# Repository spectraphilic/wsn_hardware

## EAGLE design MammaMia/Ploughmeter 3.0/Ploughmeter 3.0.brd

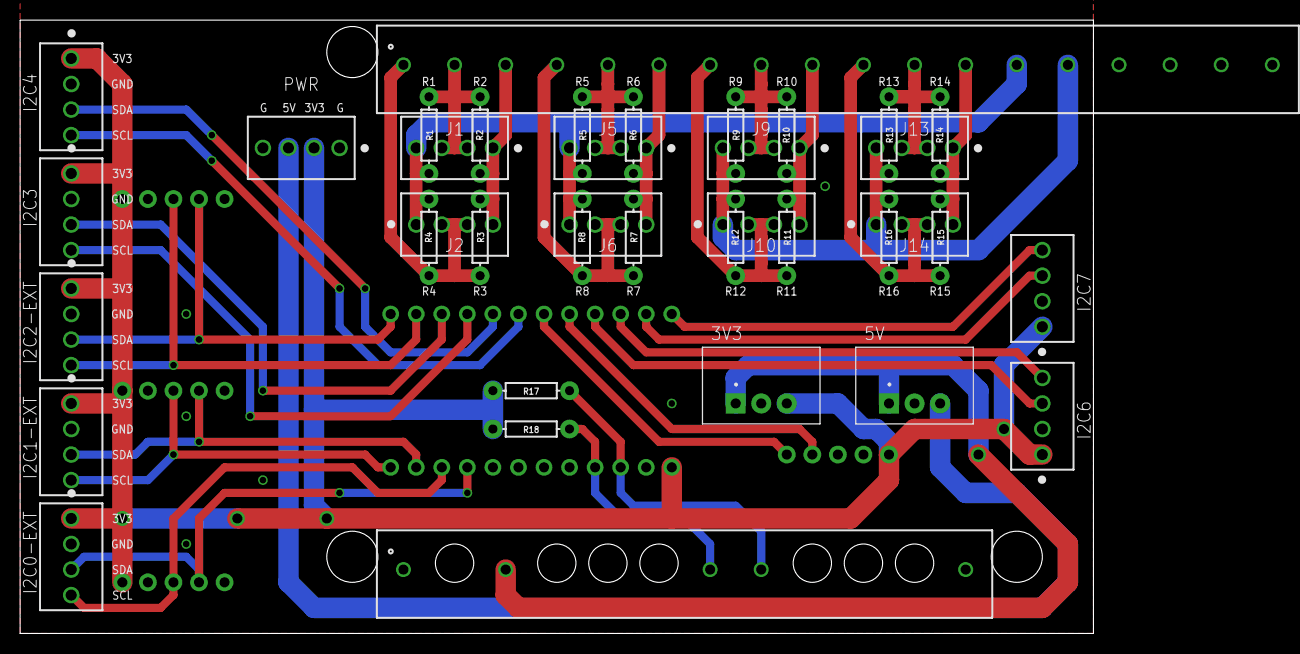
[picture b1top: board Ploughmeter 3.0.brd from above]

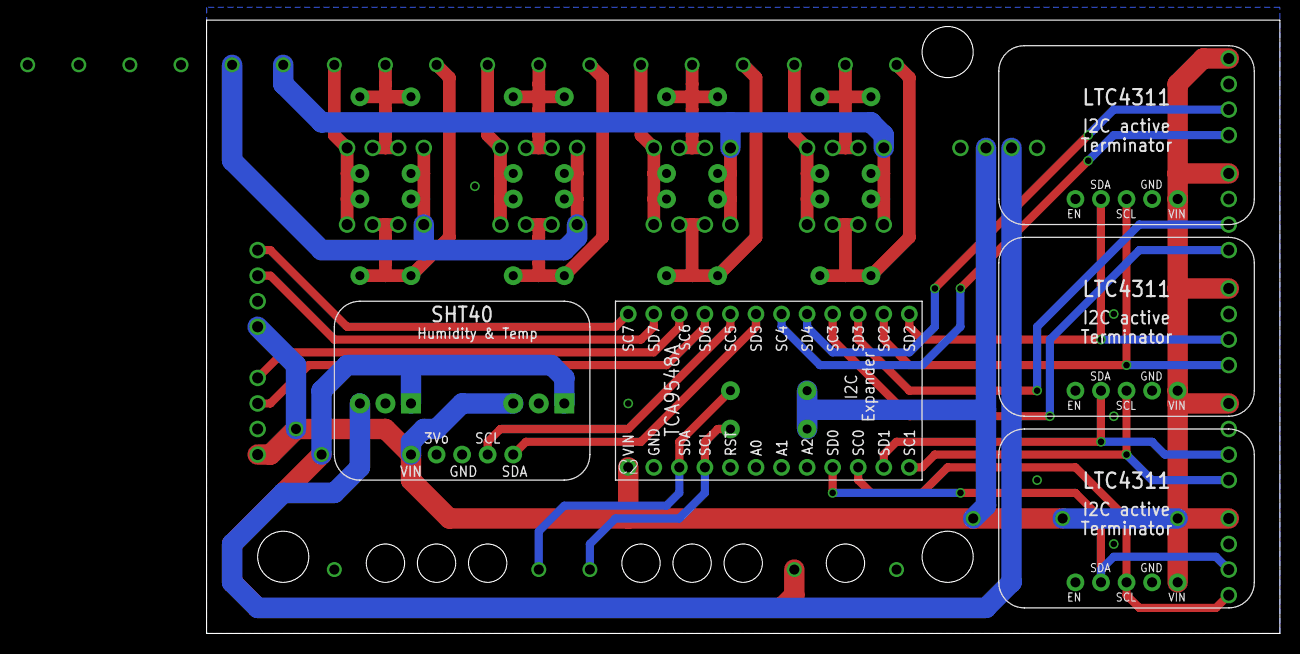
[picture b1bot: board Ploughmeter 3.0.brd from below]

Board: 2 copper layers, 106.7 x 61.0 mm, 44 parts (3 on the bottom side), 36 nets.

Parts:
3V3, 5V: 173010535
C1: WURTH_CONNECTORS_WR-TBL-PLUGGABLE-CONNECTOR_691311500018
C2: WURTH_CONNECTORS_WR-TBL-PLUGGABLE-CONNECTOR_691311500012
EX0, EX1, EX5: 1X05_ROUND_70
I2C0-EXT, I2C1-EXT, I2C2-EXT, I2C3, I2C4, I2C6, I2C7: 1725672; 1725672-4-2.54
J1, J2, J5, J6, J9, J10, J13, J14: 1725672; 1725672-4-2.54
JP2, JP4: 1X12_ROUND
JP5: 1X05_ROUND_70
PWR: 1725672; 1725672-4-2.54
R1, R2, R3, R4, R5, R6, R7, R8, R9, R10, R11, R12, R13, R14, R15, R16: 350; AXIAL-0.3
R17, R18: 10k; AXIAL-0.3

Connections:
0SCL: EX0.3, I2C0-EXT.4, JP2.10
0SDA: EX0.4, I2C0-EXT.3, JP2.9
1SCL: EX1.3, I2C1-EXT.4, JP2.12
1SDA: EX1.4, I2C1-EXT.3, JP2.11
2SCL: EX5.3, I2C2-EXT.4, JP4.2
2SDA: EX5.4, I2C2-EXT.3, JP4.1
3SCL: I2C3.4, JP4.4
3SDA: I2C3.3, JP4.3
3V3: 3V3.3, EX0.1, EX1.1, EX5.1, I2C0-EXT.1, I2C1-EXT.1, I2C2-EXT.1, I2C3.1, I2C4.1, I2C6.1, I2C7.1, JP2.1, JP5.1, PWR.2, R17.P$2, R18.P$2
4SCL: I2C4.4, JP4.6
4SDA: I2C4.3, JP4.5
5SCL: JP4.8, JP5.4
5SDA: JP4.7, JP5.5
5V: 5V.3, PWR.3
6SCL: I2C6.4, JP4.10
6SDA: I2C6.3, JP4.9
7SCL: I2C7.4, JP4.12
7SDA: I2C7.3, JP4.11
C1/SCL: C2.7, JP2.4, R18.P$1
C2/SDA: C2.8, JP2.3, R17.P$1
G1: 3V3.2, 5V.2, C2.1, C2.12, EX0.2, EX1.2, EX5.2, I2C0-EXT.2, I2C1-EXT.2, I2C2-EXT.2, I2C3.2, I2C4.2, I2C6.2, I2C7.2, JP2.2, JP5.3, PWR.1, PWR.4
SG1: C1.3, J1.1, J2.4, R2.P$1, R3.P$1
SG2: C1.6, J5.1, J6.4, R6.P$1, R7.P$1
SG3: C1.9, J9.1, J10.4, R10.P$1, R11.P$1
SG4: C1.12, J13.1, J14.4, R14.P$1, R15.P$1
SW12-2: 3V3.1, 5V.1, C2.3
U1: C1.1, J2.2, J2.3, R3.P$2, R4.P$1
U2: C1.2, J1.2, J1.3, R1.P$1, R2.P$2
U3: C1.4, J6.2, J6.3, R7.P$2, R8.P$1
U4: C1.5, J5.2, J5.3, R5.P$1, R6.P$2
U5: C1.7, J10.2, J10.3, R11.P$2, R12.P$1
U6: C1.8, J9.2, J9.3, R9.P$1, R10.P$2
U7: C1.10, J14.2, J14.3, R15.P$2, R16.P$1
U8: C1.11, J13.2, J13.3, R13.P$1, R14.P$2
U9: C1.13, J1.4, J2.1, J5.4, J6.1, R1.P$2, R4.P$2, R5.P$2, R8.P$2
U10: C1.14, J9.4, J10.1, J13.4, J14.1, R9.P$2, R12.P$2, R13.P$2, R16.P$2

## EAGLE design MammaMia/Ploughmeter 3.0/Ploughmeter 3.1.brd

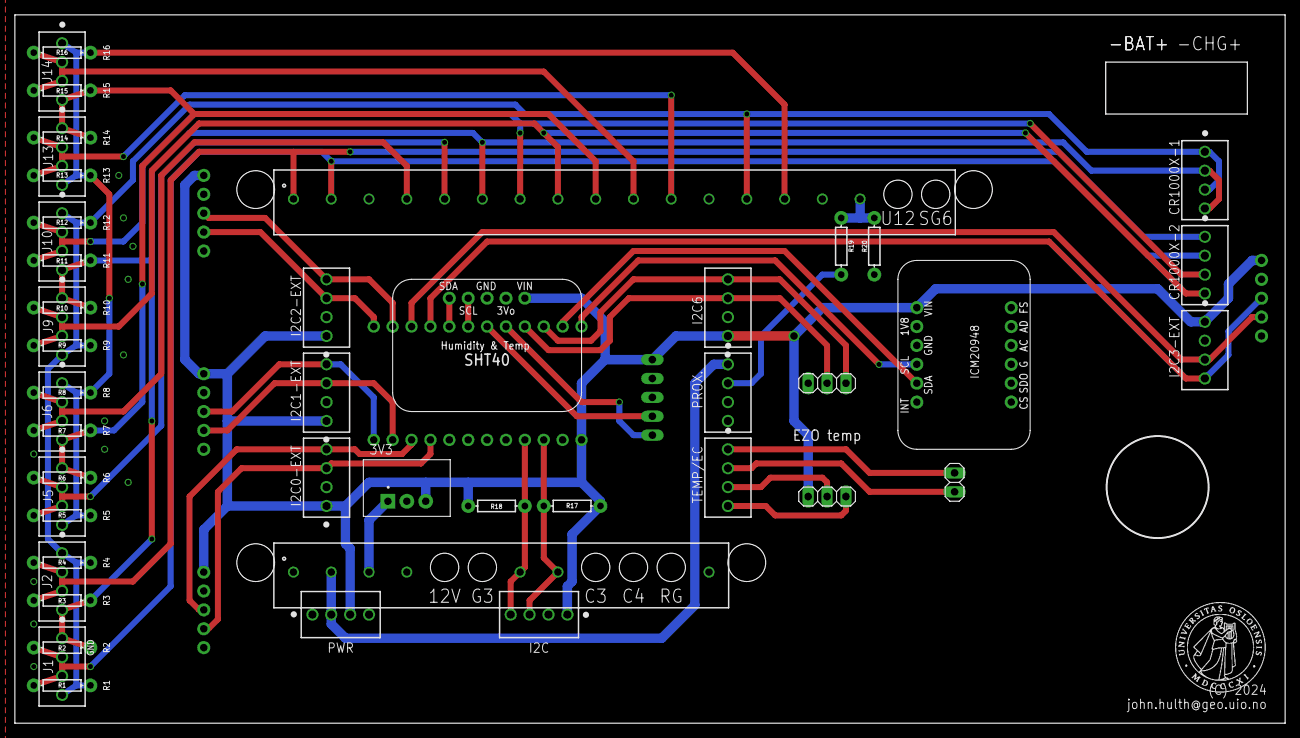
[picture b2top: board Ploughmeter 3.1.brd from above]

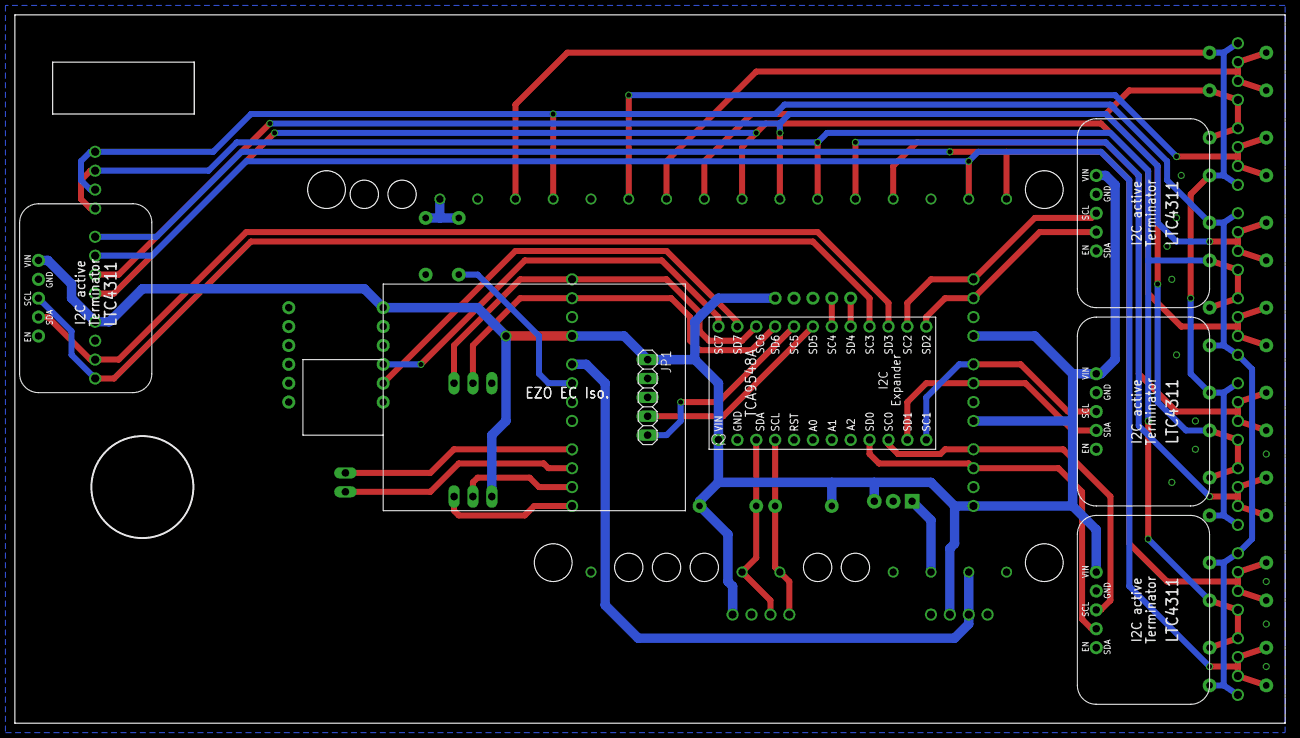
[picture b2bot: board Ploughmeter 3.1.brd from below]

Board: 2 copper layers, 170.8 x 95.2 mm, 56 parts (7 on the bottom side), 40 nets.

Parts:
3V3: 173010535
C1: WURTH_CONNECTORS_WR-TBL-PLUGGABLE-CONNECTOR_691311500018
C2: WURTH_CONNECTORS_WR-TBL-PLUGGABLE-CONNECTOR_691311500012
CR1000X-1, CR1000X-2: 1725672; 1725672-4-2.54
EX0, EX1: 1X05_ROUND_70
EX5: EX2; 1X05_ROUND_70
I2C, I2C0-EXT, I2C1-EXT, I2C2-EXT, I2C3-EXT, I2C6: 1725672; 1725672-4-2.54
J1, J2, J5, J6, J9, J10, J13, J14: 1725672; 1725672-4-2.54
JP1: 1X05
JP2, JP4: 1X12_ROUND
JP3: 1X02
JP5: 1X05_ROUND_70
JP6, JP7: 1X03
JP9: EX3; 1X05_ROUND_70
JP10, JP11: 1X06_ROUND_70
PROX.: 1725672; 1725672-4-2.54
PWR: 1725672; 1725672-4-2.54
R1, R2, R3, R4, R5, R6, R7, R8, R9, R10, R11, R12, R13, R14, R15, R16: 350; AXIAL-0.3
R17, R18: 10k; AXIAL-0.3
R19: 2k; AXIAL-0.3
R20: 1.3k; AXIAL-0.3
TEMP/EC: 1725672; 1725672-4-2.54
U$2: UIO-LOGO-BL

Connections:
0SCL: EX0.3, I2C0-EXT.4, JP2.10
0SDA: EX0.4, I2C0-EXT.3, JP2.9
1SCL: EX1.3, I2C1-EXT.4, JP2.12
1SDA: EX1.4, I2C1-EXT.3, JP2.11
2SCL: EX5.3, I2C2-EXT.4, JP4.2
2SDA: EX5.4, I2C2-EXT.3, JP4.1
3SCL: I2C3-EXT.4, JP4.4, JP9.3
3SDA: I2C3-EXT.3, JP4.3, JP9.4
3V3: 3V3.3, EX0.1, EX1.1, EX5.1, I2C.1, I2C0-EXT.1, I2C1-EXT.1, I2C2-EXT.1, I2C3-EXT.1, I2C6.1, JP1.1, JP2.1, JP5.1, JP7.1, JP9.1, JP10.1, PWR.3, R17.P$2, R18.P$2
4SCL: JP4.6, JP5.4
4SDA: JP4.5, JP5.5
5SCL: JP1.5, JP4.8
5SDA: JP1.4, JP4.7
6SCL: I2C6.4, JP4.10, JP6.1
6SDA: I2C6.3, JP4.9, JP6.2
7SCL: JP4.12, JP10.4
7SDA: JP4.11, JP10.5
C1/SCL: C2.7, I2C.4, JP2.4, R18.P$1
C2/SDA: C2.8, I2C.3, JP2.3, R17.P$1
EC+: JP3.1, TEMP/EC.1
EC-: JP3.2, TEMP/EC.2
G1: 3V3.2, C1.15, C2.1, C2.4, C2.12, EX0.2, EX1.2, EX5.2, I2C.2, I2C0-EXT.2, I2C1-EXT.2, I2C2-EXT.2, I2C3-EXT.2, I2C6.2, JP1.3, JP2.2, JP5.3, JP6.3, JP9.2, JP10.3, PROX..3, PWR.1, PWR.4, R20.P$1
PROX+: PROX..2, R19.P$2
SG2: C1.6, CR1000X-1.2, CR1000X-1.4, J1.1, J2.4, J9.1, J10.4, R2.P$1, R3.P$1, R10.P$1, R11.P$1
SG3: C1.9, J5.1, J6.4, J13.1, J14.4, R6.P$1, R7.P$1, R14.P$1, R15.P$1
SW12-1: C2.2, PROX..1, PWR.2
SW12-2: 3V3.1, C2.3
T+: JP7.2, TEMP/EC.3
T-: JP7.3, TEMP/EC.4
U1: C1.1, CR1000X-2.1, J2.2, J2.3, R3.P$2, R4.P$1
U2: C1.2, CR1000X-2.2, J1.2, J1.3, R1.P$1, R2.P$2
U3: C1.4, J6.2, J6.3, R7.P$2, R8.P$1
U4: C1.5, J5.2, J5.3, R5.P$1, R6.P$2
U5: C1.7, CR1000X-2.3, J10.2, J10.3, R11.P$2, R12.P$1
U6: C1.8, CR1000X-2.4, J9.2, J9.3, R9.P$1, R10.P$2
U7: C1.10, J14.2, J14.3, R15.P$2, R16.P$1
U8: C1.11, J13.2, J13.3, R13.P$1, R14.P$2
U9: C1.13, CR1000X-1.1, CR1000X-1.3, J1.4, J2.1, J9.4, J10.1, R1.P$2, R4.P$2, R9.P$2, R12.P$2
U10: C1.14, J5.4, J6.1, J13.4, J14.1, R5.P$2, R8.P$2, R13.P$2, R16.P$2
U11: C1.16, R19.P$1, R20.P$2

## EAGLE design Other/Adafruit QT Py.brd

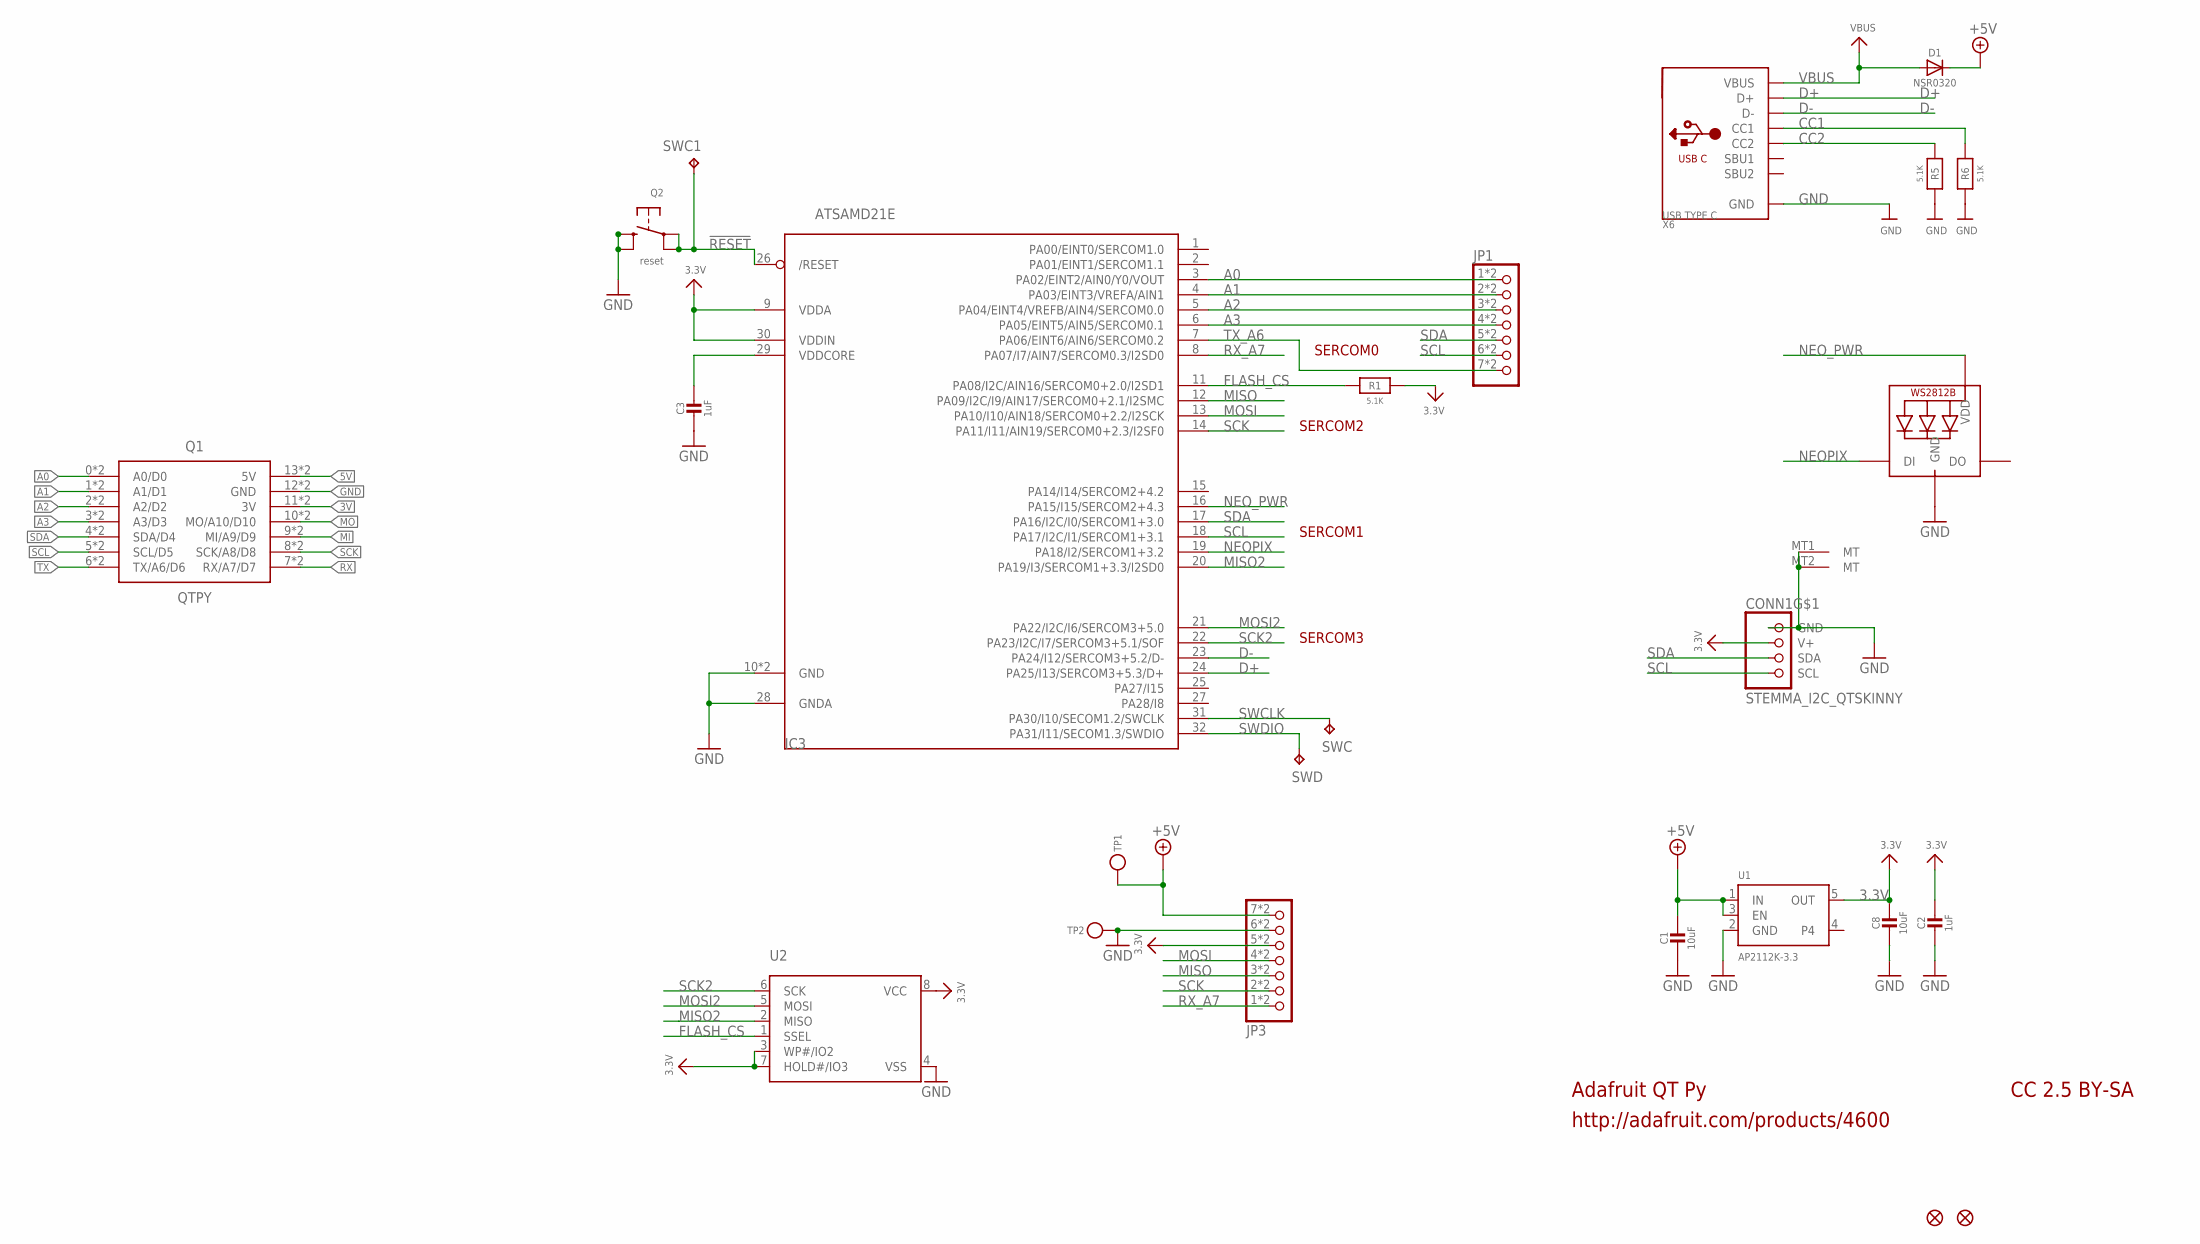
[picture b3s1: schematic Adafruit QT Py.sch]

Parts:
C1, C8: 10uF; _0805MP
C2, C3: 1uF; _0402NO
CONN1: STEMMA_I2C_QTSKINNY; JST_SH4_SKINNY
D1: NSR0320; SOD-323_MINI
IC3: ATSAMD21E; QFN32_5MM
JP1, JP3: HEADER-1X7_CASTEL; 1X07_CASTEL
LED1: WS2812B_SK6805_1515; SK6805_1515
Q1: QTPY
Q2: reset; BTN_KMR2_4.6X2.8
R1, R5, R6: 5.1K; _0402NO
SWC, SWC1: TPB1,27; B1,27
SWD: TPB1,27; B1,27
TP1, TP2: TESTPOINT_1X3; TESTPOINT_RECT_1X3MM
U1: AP2112K-3.3; SOT23-5
U2: SPIFLASH_8PIN; SOIC8_150MIL
U$6, U$8: FIDUCIAL_1MM
X6: USB TYPE C; USB_C_CUSB31-CFM2AX-01-X

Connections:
3.3V: C2.1, C8.1, CONN1.2 (V+), IC3.9 (VDDA), IC3.30 (VDDIN), JP3.5, JP3.5C (5), R1.1, U1.5 (OUT), U2.3 (WP#/IO2), U2.7 (HOLD#/IO3), U2.8 (VCC)
3V: Q1.11 (3V), Q1.11C (3V)
5V: Q1.13 (5V), Q1.13C (5V)
!RESET: IC3.26 (/RESET), Q2.A, Q2.A' (P1), SWC1.TP
+5V: C1.1, D1.C, JP3.7, JP3.7C (7), TP1.P$1, U1.1 (IN), U1.3 (EN)
A0: IC3.3 (PA02/EINT2/AIN0/Y0/VOUT), JP1.1, JP1.1C (1), Q1.0 (A0/D0), Q1.0C (A0/D0)
A1: IC3.4 (PA03/EINT3/VREFA/AIN1), JP1.2, JP1.2C (2), Q1.1 (A1/D1), Q1.1C (A1/D1)
A2: IC3.5 (PA04/EINT4/VREFB/AIN4/SERCOM0.0), JP1.3, JP1.3C (3), Q1.2 (A2/D2), Q1.2C (A2/D2)
A3: IC3.6 (PA05/EINT5/AIN5/SERCOM0.1), JP1.4, JP1.4C (4), Q1.3 (A3/D3), Q1.3C (A3/D3)
CC1: R6.2, X6.A5 (CC1)
CC2: R5.2, X6.B5 (CC2)
D+: IC3.24 (PA25/I13/SERCOM3+5.3/D+), X6.A6 (D+), X6.B6 (D+)
D-: IC3.23 (PA24/I12/SERCOM3+5.2/D-), X6.A7 (D-), X6.B7 (D-)
FLASH_CS: IC3.11 (PA08/I2C/AIN16/SERCOM0+2.0/I2SD1), R1.2, U2.1 (SSEL)
GND: C1.2, C2.2, C3.2, C8.2, CONN1.1 (GND), CONN1.MT1 (MT), CONN1.MT2 (MT), IC3.10 (GND), IC3.28 (GNDA), IC3.33 (GND), JP3.6, JP3.6C (6), LED1.4 (GND), Q1.12 (GND), Q1.12C (GND), Q2.B (S), Q2.B' (S1), R5.1, R6.1, TP2.P$1, U1.2 (GND), U2.4 (VSS), X6.A1B12 (GND), X6.B1A12 (GND)
MI: Q1.9 (MI/A9/D9), Q1.9C (MI/A9/D9)
MISO: IC3.12 (PA09/I2C/I9/AIN17/SERCOM0+2.1/I2SMC), JP3.3, JP3.3C (3)
MISO2: IC3.20 (PA19/I3/SERCOM1+3.3/I2SD0), U2.2 (MISO)
MO: Q1.10 (MO/A10/D10), Q1.10C (MO/A10/D10)
MOSI: IC3.13 (PA10/I10/AIN18/SERCOM0+2.2/I2SCK), JP3.4, JP3.4C (4)
MOSI2: IC3.21 (PA22/I2C/I6/SERCOM3+5.0), U2.5 (MOSI)
NEOPIX: IC3.19 (PA18/I2/SERCOM1+3.2), LED1.1 (DI)
NEO_PWR: IC3.16 (PA15/I15/SERCOM2+4.3), LED1.2 (VDD)
RX: Q1.7 (RX/A7/D7), Q1.7C (RX/A7/D7)
RX_A7: IC3.8 (PA07/I7/AIN7/SERCOM0.3/I2SD0), JP3.1, JP3.1C (1)
SCK: IC3.14 (PA11/I11/AIN19/SERCOM0+2.3/I2SF0), JP3.2, JP3.2C (2), Q1.8 (SCK/A8/D8), Q1.8C (SCK/A8/D8)
SCK2: IC3.22 (PA23/I2C/I7/SERCOM3+5.1/SOF), U2.6 (SCK)
SCL: CONN1.4 (SCL), IC3.18 (PA17/I2C/I1/SERCOM1+3.1), JP1.6, JP1.6C (6), Q1.5 (SCL/D5), Q1.5C (SCL/D5)
SDA: CONN1.3 (SDA), IC3.17 (PA16/I2C/I0/SERCOM1+3.0), JP1.5, JP1.5C (5), Q1.4 (SDA/D4), Q1.4C (SDA/D4)
SWCLK: IC3.31 (PA30/I10/SECOM1.2/SWCLK), SWC.TP
SWDIO: IC3.32 (PA31/I11/SECOM1.3/SWDIO), SWD.TP
TX: Q1.6 (TX/A6/D6), Q1.6C (TX/A6/D6)
TX_A6: IC3.7 (PA06/EINT6/AIN6/SERCOM0.2), JP1.7, JP1.7C (7)
VBUS: D1.A, X6.A4B9 (VBUS), X6.B4A9 (VBUS)
VDDCORE: C3.1, IC3.29 (VDDCORE)

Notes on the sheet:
Adafruit QT Py
http://adafruit.com/products/4600
CC 2.5 BY-SA
SERCOM0
SERCOM1
SERCOM2
SERCOM3

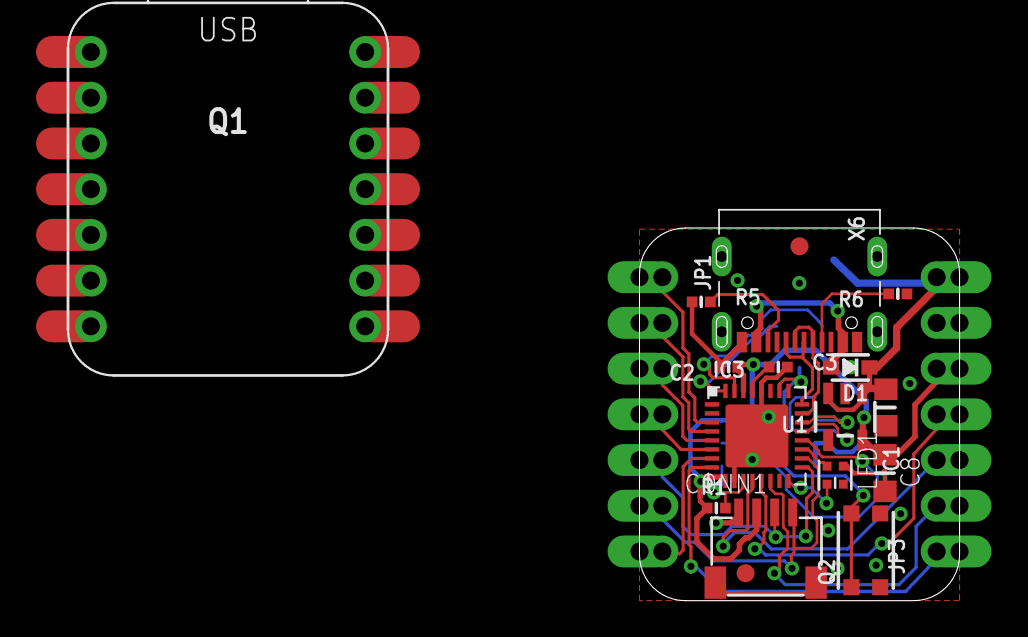
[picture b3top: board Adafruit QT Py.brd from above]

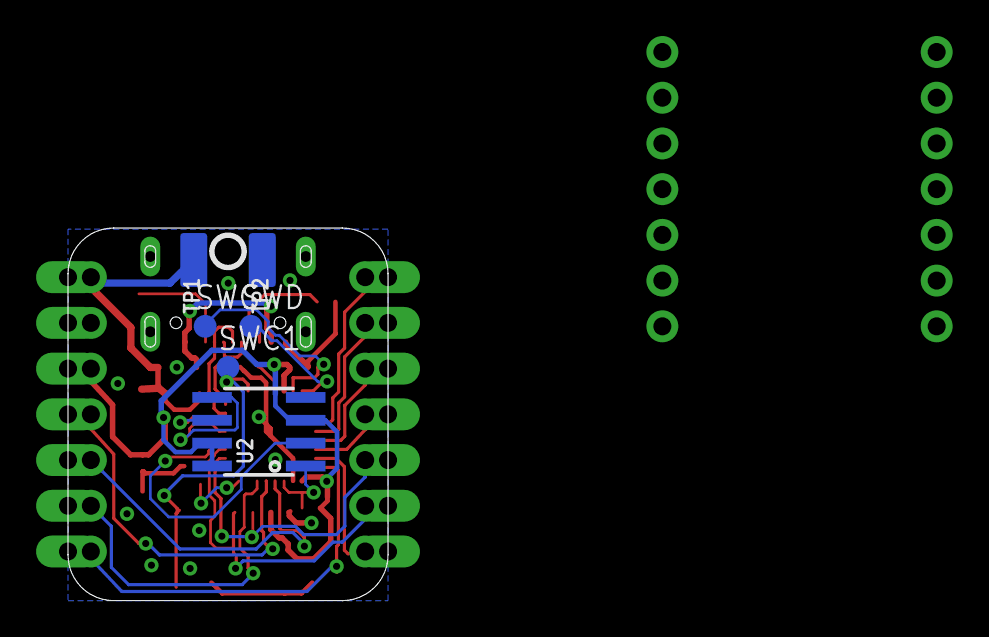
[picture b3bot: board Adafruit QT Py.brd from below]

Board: 2 copper layers, 17.8 x 20.7 mm, 28 parts (8 on the bottom side), 35 nets.

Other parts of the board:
U$11: QTPY_BOT
U$12: PCBFEAT-REV-040
U$13: QTPY_TOP

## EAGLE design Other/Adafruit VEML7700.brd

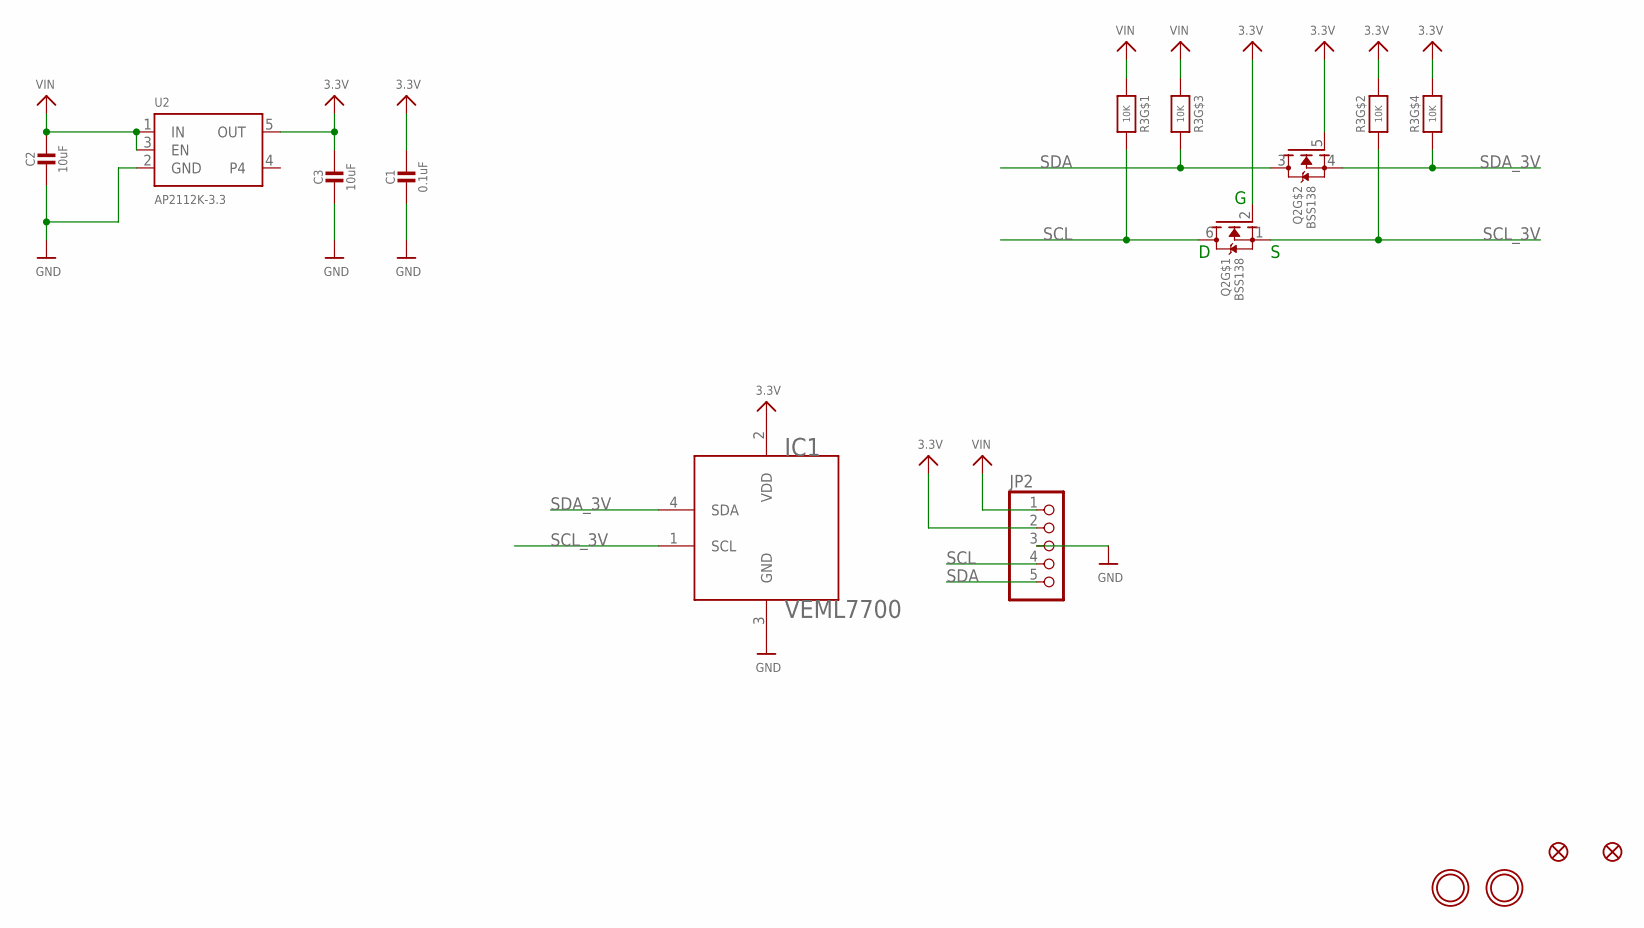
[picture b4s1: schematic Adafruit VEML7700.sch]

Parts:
C1: 0.1uF; 0603-NO
C2, C3: 10uF; 0805-NO
FID1, FID2: FIDUCIAL_1MM
IC1: VEML7700
JP2: HEADER-1X5ROUND; 1X05_ROUND
Q2: BSS138; SOT363
R3: 10K; RESPACK_4X0603
U2: AP2112K-3.3; SOT23-5
U$3, U$4: MOUNTINGHOLE2.5; MOUNTINGHOLE_2.5_PLATED

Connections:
3.3V: C1.1, C3.1, IC1.2 (VDD), JP2.2, Q2.2 (G), Q2.5 (G), R3.2 (1), R3.4 (1), U2.5 (OUT)
GND: C1.2, C2.2, C3.2, IC1.3 (GND), JP2.3, U2.2 (GND)
SCL: JP2.4, Q2.6 (D), R3.8 (2)
SCL_3V: IC1.1 (SCL), Q2.1 (S), R3.7 (2)
SDA: JP2.5, Q2.3 (D), R3.6 (2)
SDA_3V: IC1.4 (SDA), Q2.4 (S), R3.5 (2)
VIN: C2.1, JP2.1, R3.1, R3.3 (1), U2.1 (IN), U2.3 (EN)

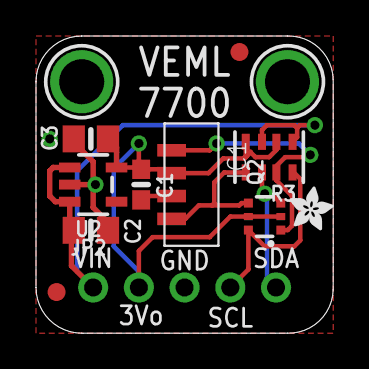
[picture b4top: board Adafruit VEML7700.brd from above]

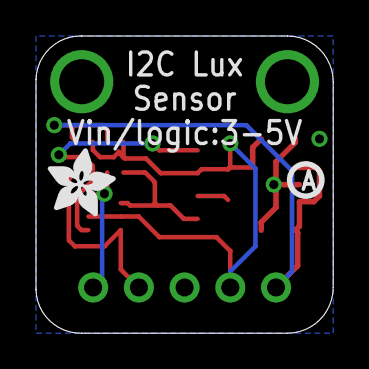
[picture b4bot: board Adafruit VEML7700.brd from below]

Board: 2 copper layers, 16.5 x 16.5 mm, 16 parts (3 on the bottom side), 7 nets.

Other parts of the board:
U$1: ADAFRUIT_3.5MM
U$8: ADAFRUIT_2.5MM
U$12: KATTNI_STOP
U$27: PCBFEAT-REV-040

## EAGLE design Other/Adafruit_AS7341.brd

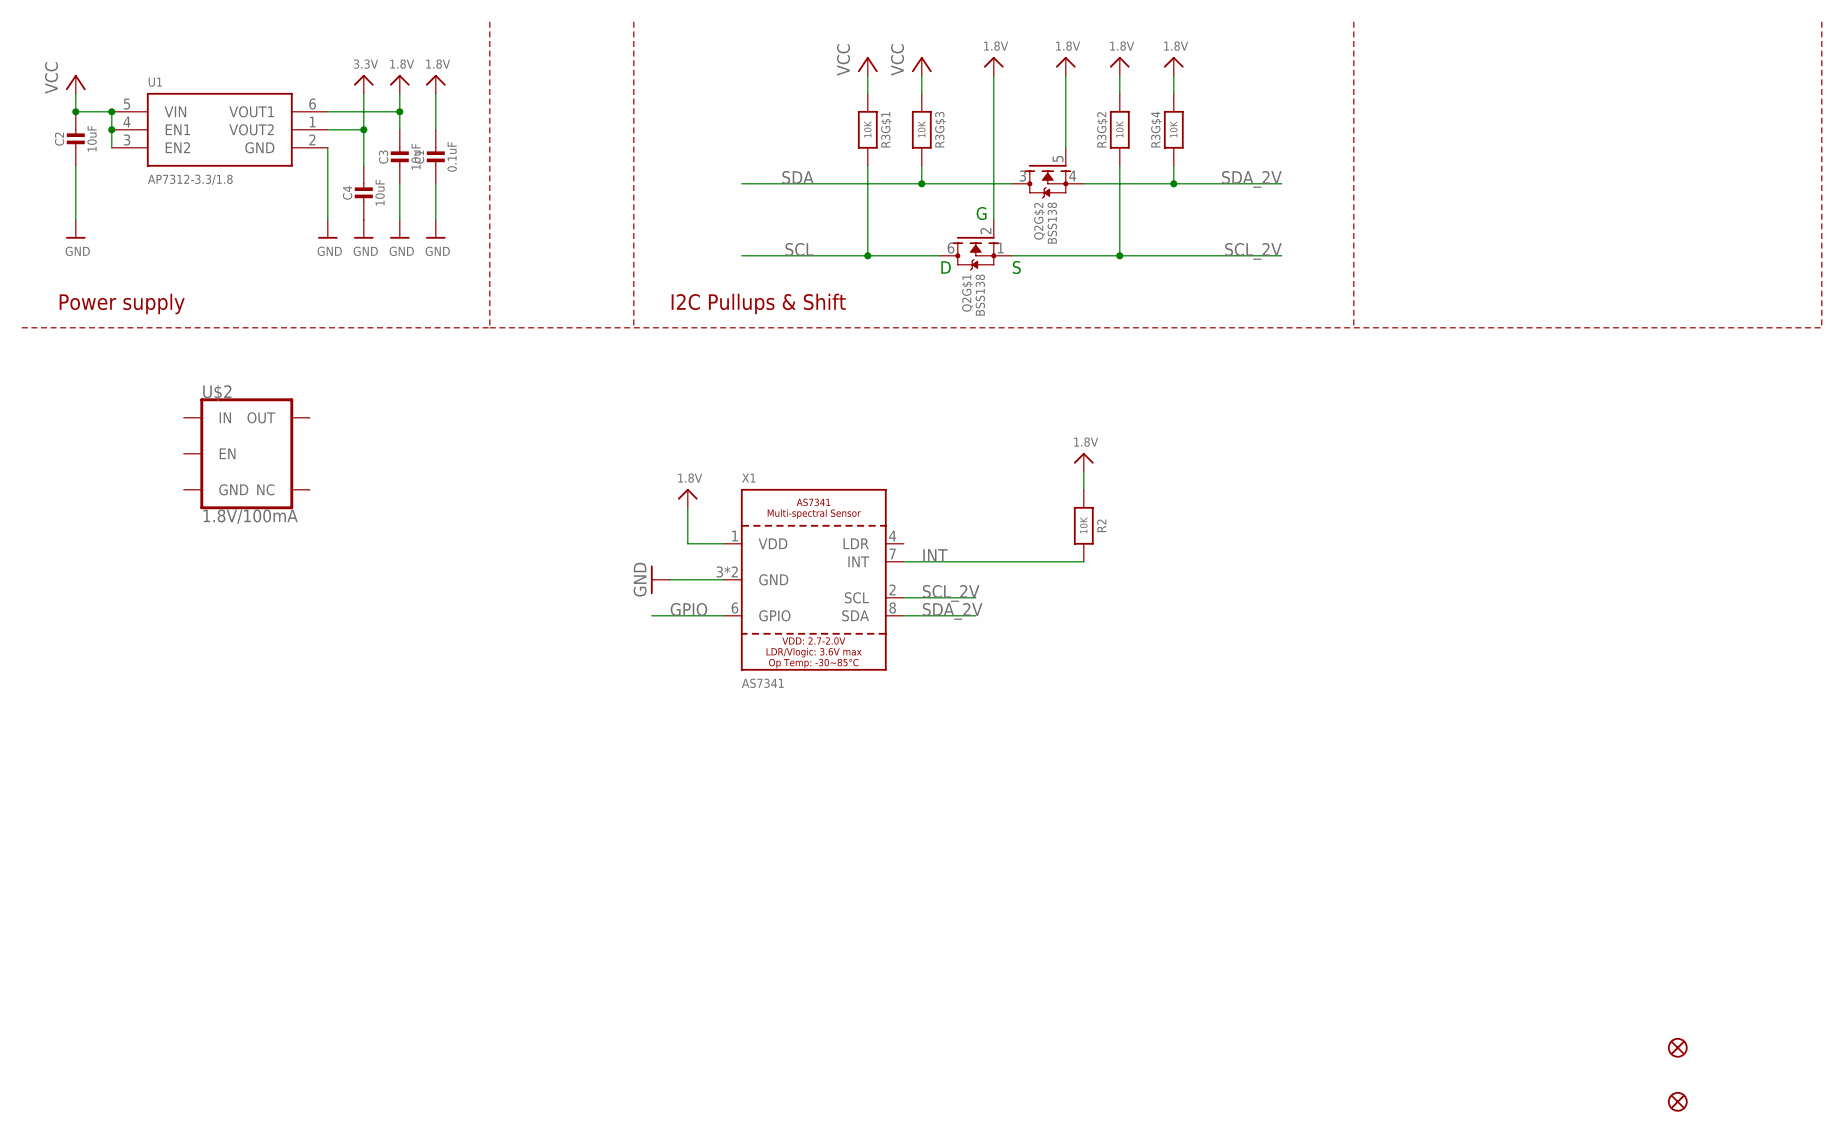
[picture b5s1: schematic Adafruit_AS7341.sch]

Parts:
C1: 0.1uF; 0603-NO
C2, C3, C4: 10uF; 0805-NO
FID3, FID4: FIDUCIAL_1MM
Q2: BSS138; SOT363
R2: 10K; 0603-NO
R3: 10K; RESPACK_4X0603
U1: AP7312-3.3/1.8; SOT23-6
U$2: 1.8V/100mA; SC70
X1: AS7341

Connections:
1.8V: C1.1, C3.1, Q2.2 (G), Q2.5 (G), R2.1, R3.2 (1), R3.4 (1), U1.6 (VOUT1), X1.1 (VDD)
3.3V: C4.1, U1.1 (VOUT2)
GND: C1.2, C2.2, C3.2, C4.2, U1.2 (GND), X1.3 (GND), X1.5 (GND)
GPIO: X1.6 (GPIO)
INT: R2.2, X1.7 (INT)
SCL: Q2.6 (D), R3.8 (2)
SCL_2V: Q2.1 (S), R3.7 (2), X1.2 (SCL)
SDA: Q2.3 (D), R3.6 (2)
SDA_2V: Q2.4 (S), R3.5 (2), X1.8 (SDA)
VCC: C2.1, R3.1, R3.3 (1), U1.3 (EN2), U1.4 (EN1), U1.5 (VIN)

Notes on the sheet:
I2C Pullups & Shift
Power supply

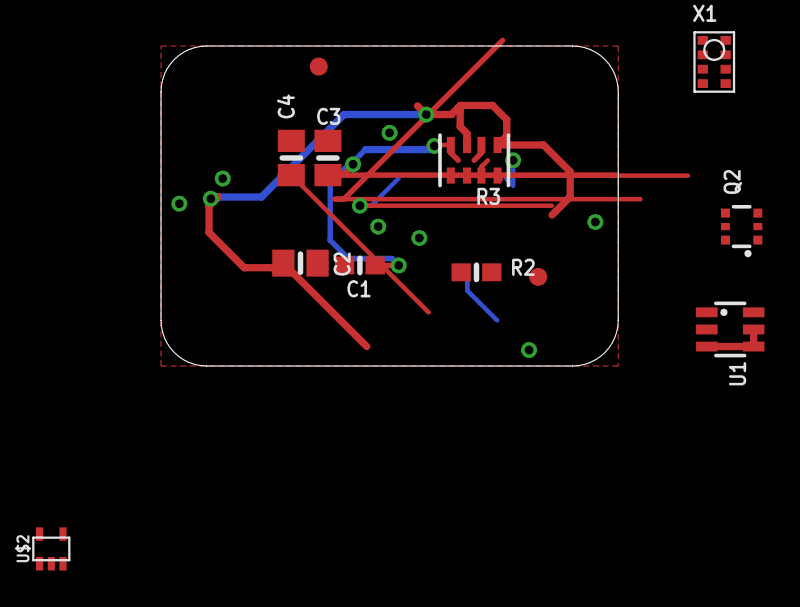
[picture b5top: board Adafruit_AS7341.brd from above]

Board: 2 copper layers, 25.4 x 17.8 mm, 12 parts (0 on the bottom side), 9 nets.

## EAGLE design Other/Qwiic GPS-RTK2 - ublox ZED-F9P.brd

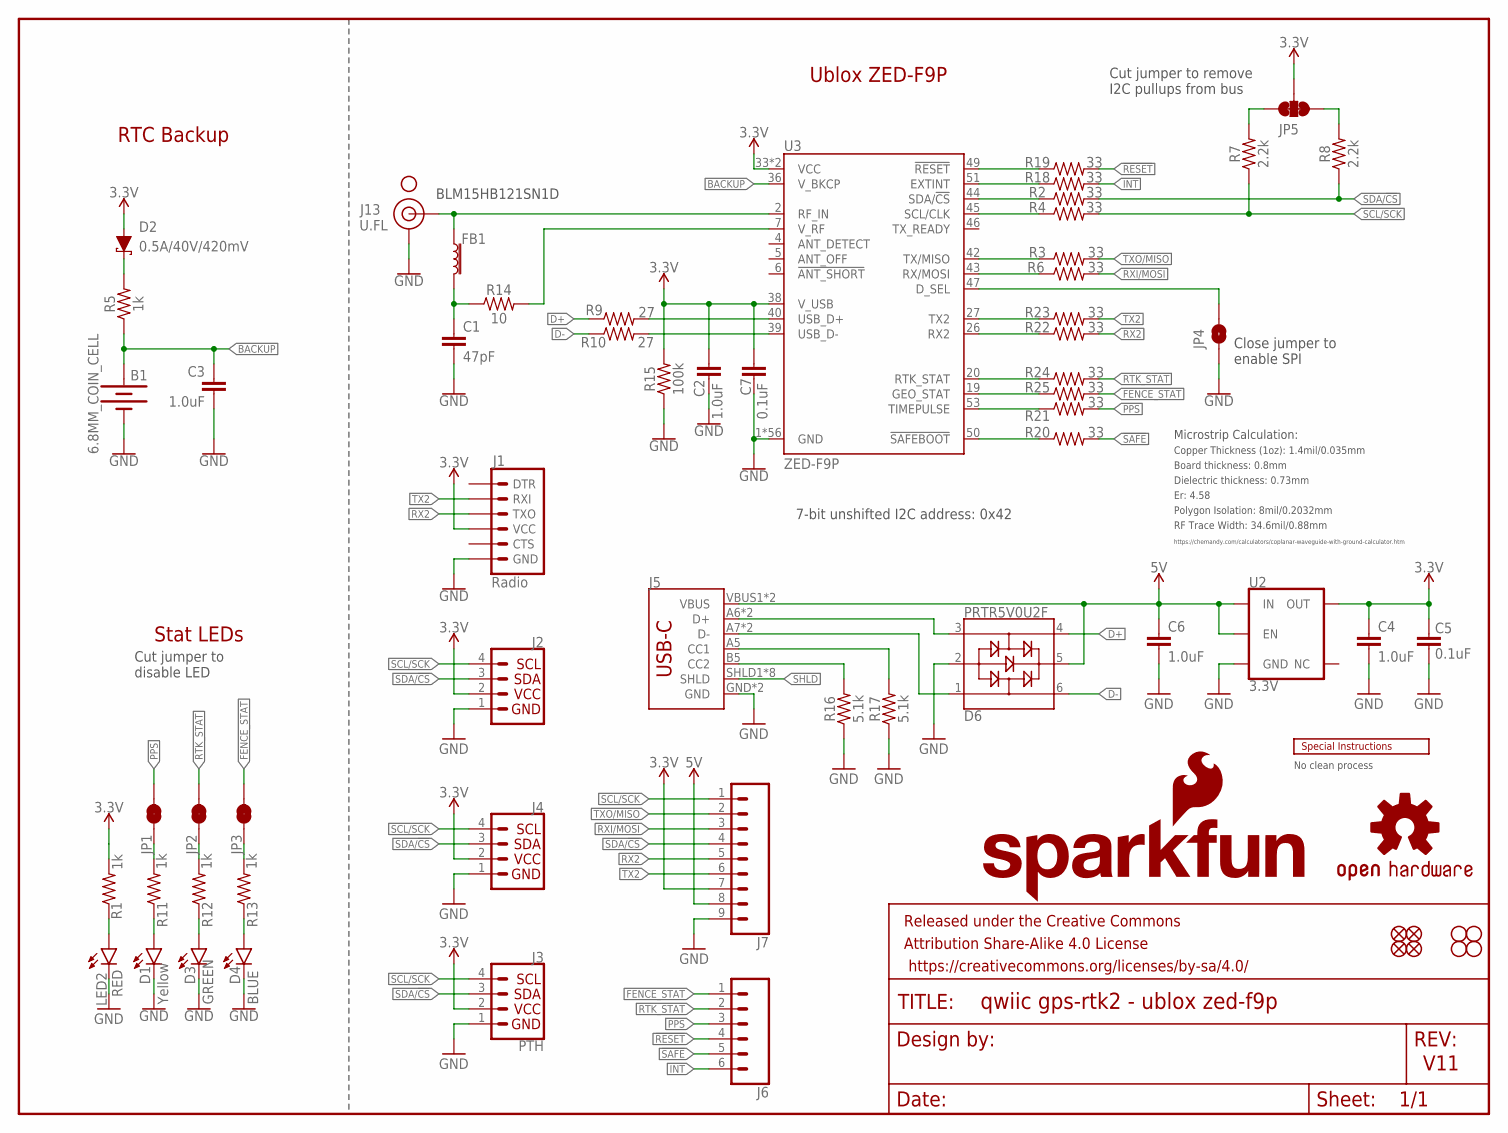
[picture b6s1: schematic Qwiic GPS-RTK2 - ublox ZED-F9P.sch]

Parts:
B1: 6.8MM_COIN_CELL; BATTCON-6.8MM
C1: 47pF; 0603
C2, C3, C4, C6: 1.0uF; 0603
C5, C7: 0.1uF; 0603
D1: Yellow; LED-0603
D2: 0.5A/40V/420mV; SOD-323
D3: GREEN; LED-0603
D4: BLUE; LED-0603
D6: PRTR5V0U2F; SOT886
FB1: FERRITE_BEAD-120_OHM-0402; 0402
FRAME1: FRAME-LETTER; CREATIVE_COMMONS
J1: Radio; 1X06_NO_SILK
J2, J4: I2C_STANDARDQWIIC; 1X04_1MM_RA
J3: PTH; 1X04_NO_SILK
J5: USB_C16PIN; USB-C-16P
J6: CONN_06NO_SILK_FEMALE_PTH; 1X06_NO_SILK
J7: CONN_09NO_SILK; 1X09_NO_SILK
J13: U.FL
JP1, JP2, JP3: JUMPER-SMT_2_NC_TRACE_SILK; SMT-JUMPER_2_NC_TRACE_SILK
JP4: JUMPER-SMT_2_NO_SILK; SMT-JUMPER_2_NO_SILK
JP5: JUMPER-SMT_3_2-NC_TRACE_SILK; SMT-JUMPER_3_2-NC_TRACE_SILK
JP21, JP61, JP71, JP81: FIDUCIALUFIDUCIAL; MICRO-FIDUCIAL
JP31, JP41, JP91, JP101: STAND-OFF
LED2: RED; LED-0603
LOGO1: OSHW-LOGOMINI; OSHW-LOGO-MINI
LOGO2: SFE_LOGO_NAME_FLAME.1_INCH; SFE_LOGO_NAME_FLAME_.1
R1, R5, R11, R12, R13: 1k; 0603
R2, R3, R4, R6, R18, R19, R20, R21, R22, R23, R24, R25: 33; 0603
R7, R8: 2.2k; 0603
R9, R10: 27; 0603
R14: 10; 0603
R15: 100k; 0603
R16, R17: 5.1k; 0603
U2: 3.3V; SOT23-5
U3: ZED-F9P
U$2: SPECIAL_INSTRUCTIONS-ORDERING; ORDERING_INSTRUCTIONS
U$54: SMA-ANTENNA-THREADED; SMA-THREADED

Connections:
3.3V: C2.1, C4.1, C5.2, C7.2, D2.A, J1.4 (VCC), J2.2, J3.2 (VCC), J4.2, J7.7, JP5.2, R1.2, R15.2, U2.5 (OUT), U3.33 (VCC), U3.34 (VCC), U3.38 (V_USB)
5V: C6.1, D6.5, J5.VBUS1 (VBUS), J5.VBUS2 (VBUS), J7.8, U2.1 (IN), U2.3 (EN)
!RESET: J6.4, R19.2
!SAFE: J6.5, R20.2
ANT_VCC: C1.1, FB1.2, R14.1
BACKUP: B1.+, C3.1, R5.1, U3.36 (V_BKCP)
CC1: J5.A5 (CC1), R17.2
CC2: J5.B5 (CC2), R16.2
D+: D6.4, R9.1
D-: D6.6, R10.1
D_SEL: JP4.2, U3.47 (D_SEL)
FENCE_STAT: J6.1, JP3.2, R25.2
GND: B1.-, C1.2, C2.2, C3.2, C4.2, C5.1, C6.2, C7.1, D1.C, D3.C, D4.C, D6.2, J1.6 (GND), J2.1, J3.1 (GND), J4.1, J5.GND, J5.GND2 (GND), J7.9, J13.1 (GND), J13.2 (GND), JP4.1, LED2.C, R15.1, R16.1, R17.1, U2.2 (GND), U3.1 (GND), U3.3 (GND), U3.12 (GND), U3.14 (GND), U3.32 (GND), U3.37 (GND), U3.41 (GND), U3.48 (GND), U3.55 (GND), U3.56 (GND), U3.57 (GND), U3.58 (GND), U3.59 (GND), U3.60 (GND), U3.61 (GND), U3.62 (GND), U3.63 (GND), U3.64 (GND), U3.65 (GND), U3.66 (GND), U3.67 (GND), U3.68 (GND), U3.69 (GND), U3.70 (GND), U3.71 (GND), U3.72 (GND), U3.73 (GND), U3.74 (GND), U3.75 (GND), U3.76 (GND), U3.77 (GND), U3.78 (GND), U3.79 (GND), U3.80 (GND), U3.81 (GND), U3.82 (GND), U3.83 (GND), U3.84 (GND), U3.85 (GND), U3.86 (GND), U3.87 (GND), U3.88 (GND), U3.89 (GND), U3.90 (GND), U3.91 (GND), U3.92 (GND), U3.93 (GND), U3.94 (GND), U3.95 (GND), U3.96 (GND), U3.97 (GND), U3.98 (GND), U3.99 (GND), U3.100 (GND), U3.101 (GND), U3.102 (GND)
GPS_ANT1: FB1.1, J13.FEED (SIGNAL), U3.2 (RF_IN)
INT: J6.6, R18.2
unnamed: D3.A, R12.1
unnamed: D1.A, R11.1
unnamed: JP2.1, R12.2
unnamed: JP1.1, R11.2
unnamed: JP5.1, R8.2
unnamed: D2.C, R5.2
unnamed: D4.A, R13.1
unnamed: JP5.3, R7.2
unnamed: JP3.1, R13.2
unnamed: LED2.A, R1.1
unnamed: R9.2, U3.40 (USB_D+)
unnamed: R10.2, U3.39 (USB_D-)
unnamed: R14.2, U3.7 (V_RF)
unnamed: R22.1, U3.26 (RX2)
unnamed: R18.1, U3.51 (EXTINT)
unnamed: R19.1, U3.49 (!RESET!)
unnamed: R21.1, U3.53 (TIMEPULSE)
unnamed: R20.1, U3.50 (!SAFEBOOT!)
unnamed: R24.1, U3.20 (RTK_STAT)
unnamed: R25.1, U3.19 (GEO_STAT)
PPS: J6.3, JP1.2, R21.2
RTK_STAT: J6.2, JP2.2, R24.2
RX2: J1.3 (TXO), J7.5, R22.2
RXI/MOSI: J7.3, R6.2
RXLV: R6.1, U3.43 (RX/MOSI)
SCL/SCK: J2.4, J3.4 (SCL), J4.4, J7.1, R4.2, R7.1
SCL_LV: R4.1, U3.45 (SCL/CLK)
SDA/!CS: J2.3, J3.3 (SDA), J4.3, J7.4, R2.2, R8.1
SDA_LV: R2.1, U3.44 (SDA/!CS!)
SHLD: J5.SHLD1 (SHLD), J5.SHLD2 (SHLD), J5.SHLD3 (SHLD), J5.SHLD4 (SHLD), J5.SHLD5 (SHLD), J5.SHLD6 (SHLD), J5.SHLD7 (SHLD), J5.SHLD8 (SHLD)
TX2: J1.2 (RXI), J7.6, R23.2
TX2_P: R23.1, U3.27 (TX2)
TXLV: R3.1, U3.42 (TX/MISO)
TXO/MISO: J7.2, R3.2
UNP_D+: D6.3, J5.A6 (D+), J5.B6 (D+)
UNP_D-: D6.1, J5.A7 (D-), J5.B7 (D-)

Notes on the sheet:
V11
7-bit unshifted I2C address: 0x42
Ublox ZED-F9P
RTC Backup
Stat LEDs
Cut jumper to remove I2C pullups from bus
Cut jumper to disable LED
Close jumper to enable SPI
BLM15HB121SN1D
Board thickness: 0.8mm
Er: 4.58
Copper Thickness (1oz): 1.4mil/0.035mm
RF Trace Width: 34.6mil/0.88mm
Polygon Isolation: 8mil/0.2032mm
No clean process
Dielectric thickness: 0.73mm
https://chemandy.com/calculators/coplanar-waveguide-with-ground-calculator.htm
Microstrip Calculation:

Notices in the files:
MammaMia/Ploughmeter 3.0/Ploughmeter 3.1.brd:
(C) 2024
parts and their libraries:
SparkFun-Resistors: Licensing: Creative Commons ShareAlike 4.0 International - https://creativecommons.org/licenses/by-sa/4.0
microbuilder: This work is placed in the public domain, and may be freely used for commercial and non-commercial work with the following conditions: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
